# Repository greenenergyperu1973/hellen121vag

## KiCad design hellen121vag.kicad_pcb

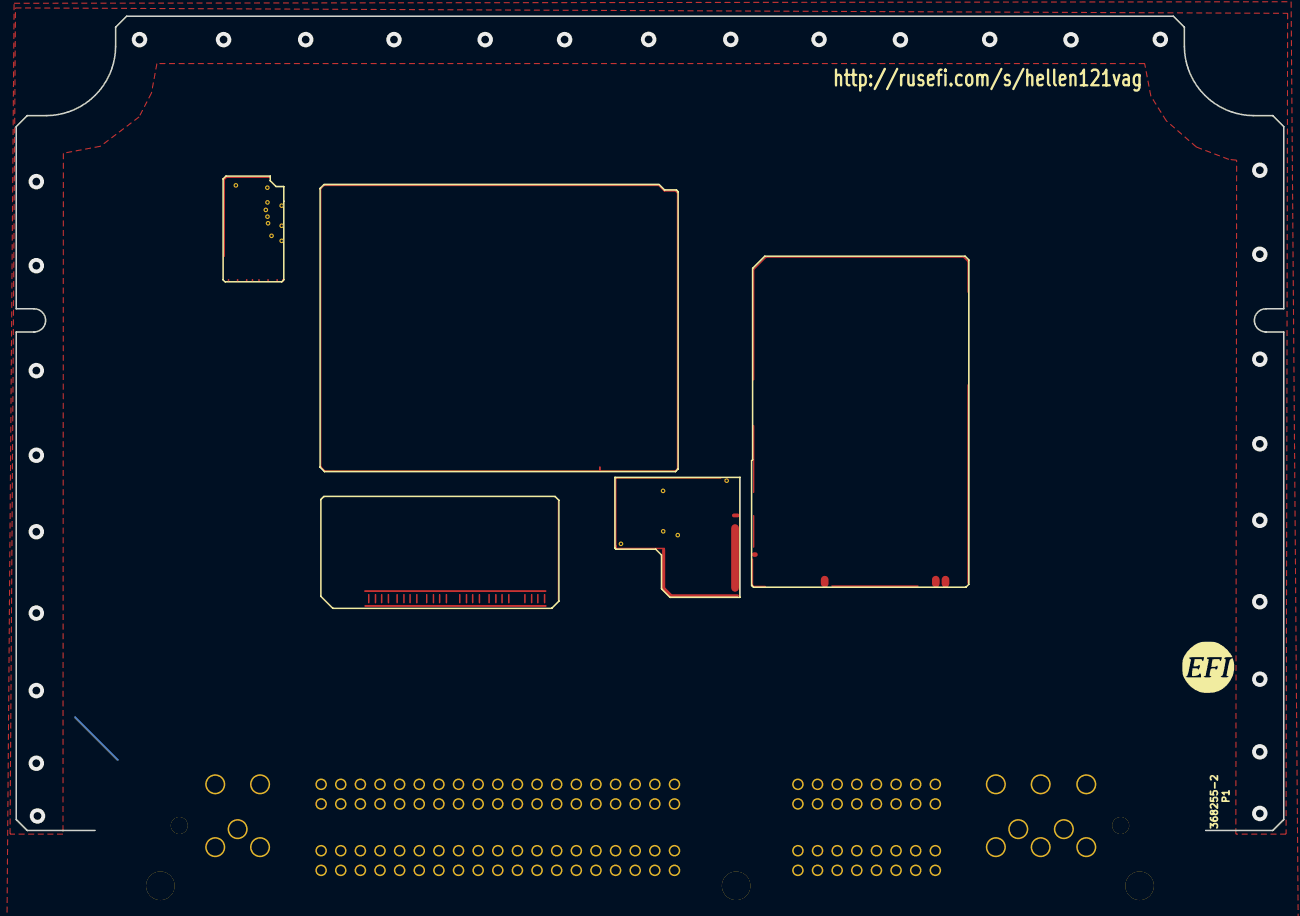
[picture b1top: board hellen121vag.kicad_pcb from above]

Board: 4 copper layers, 164.0 x 105.4 mm, 7 parts (0 on the bottom side), 108 nets.

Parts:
G7: LOGO
M3: Module-mcu-0.7; mcu
M4: Module-input-0.1; input
M6: Module-output-0.3; output
M7: Module-ign8-0.2; ign8
M8: Module-power12-0.2; power12
P1: 368255-2

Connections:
+5V: M3.S1 (V5), M4.E2 (V5), M6.W14 (V5), M8.E1 (V5)
+5VA: M3.S33 (V5A), M4.E5 (V5A), M4.J1 (PULL_V5A), M4.J5 (PULL_PPS), M4.J7 (PULL_AUX4), M4.J9 (PULL_AUX2), M4.J10 (PULL_AUX1), M4.J17 (PULL_CAM), M4.J18 (PULL_VSS), M4.J19 (PULL_TPS), M4.J20 (PULL_O2S), M4.J21 (PULL_CRANK), M4.N1 (V5A)
+5VP: P1.53, P1.72, P1.73, P1.83, P1.98
+12V_RAW: M6.S11 (V12_RAW), M8.E2 (V12_RAW)
/A1: M3.S30 (IN_O2S2), M4.N4 (O2S2)
/A2: M3.S22 (IN_MAP3), M4.N12 (MAP3)
/A3: M3.S26 (IN_AUX3), M4.N8 (AUX3)
/A4: M3.S23 (IN_DIG3), M4.N11 (RES3)
/AFR: M3.S16 (IN_O2S), M4.N18 (O2S)
/CAM1: M3.S15 (IN_AN_DIG2), M4.N19 (CAM)
/CAM2: M3.S27 (IN_AUX4), M4.N7 (AUX4)
/CHECK_ENGINE: M3.E22 (OUT_IO8), M6.W25 (LOW6_DIODE)
/CLT: M3.S18 (IN_CLT), M4.N16 (CLT)
/CRANK: M3.S13 (IN_AN_DIG1), M4.N21 (CRANK)
/D1: M3.S3 (IN_DIG8), M4.N26 (SENS1)
/D2: M3.S4 (IN_DIG9), M4.N25 (SENS2)
/D3: M3.S5 (IN_DIG10), M4.N24 (SENS3)
/D4: M3.S6 (IN_DIG11), M4.N23 (SENS4)
/FUEL_CONSUM: M3.E19 (OUT_PWM7), M6.W22 (PP2)
/FUEL_PUMP_RELAY: M3.E8 (OUT_IO1), M6.W35 (LOW11)
/IAT: M3.S19 (IN_IAT), M4.N15 (IAT)
/IDLE: M3.E23 (OUT_IO4), M6.W38 (LOW3_DUAL)
/IGN1: M3.W1 (OUT_IGN1), M7.V8 (IGN1)
/IGN2: M3.W2 (OUT_IGN2), M7.V7 (IGN2)
/IGN3: M3.W3 (OUT_IGN3), M7.V6 (IGN3)
/IGN4: M3.W4 (OUT_IGN4), M7.V5 (IGN4)
/IGN5: M3.W5 (OUT_IGN5), M7.V4 (IGN5)
/IGN6: M3.W6 (OUT_IGN6), M7.V3 (IGN6)
/IGN7: M3.W7 (OUT_IGN7), M7.V2 (IGN7)
/IGN8: M3.W8 (OUT_IGN8), M7.V1 (IGN8)
/IGN_V5: M3.W9 (IGN_V5), M7.V9 (VCC)
/IGN_V33: M3.W10 (IGN_V33), M7.V10 (V33)
/INJ1: M3.E25 (OUT_INJ1), M6.W24 (INJ1)
/INJ2: M3.E26 (OUT_INJ2), M6.W23 (INJ2)
/INJ3: M3.E29 (OUT_INJ3), M6.W20 (INJ3)
/INJ4: M3.E30 (OUT_INJ4), M6.W19 (INJ4)
/INJ5: M3.E31 (OUT_INJ5), M6.W18 (INJ5)
/INJ6: M3.E32 (OUT_INJ6), M6.W17 (INJ6)
/INJ7: M3.E33 (OUT_INJ7), M6.W16 (INJ7)
/INJ8: M3.E34 (OUT_INJ8), M6.W15 (INJ8)
/IN_AFR: M4.S9 (IN_O2S), P1.14
/IN_CAM1: M4.S5 (IN_CAM), P1.86
/IN_CAM2: M4.S21 (IN_AUX4), P1.87
/IN_CLT: M4.S15 (IN_CLT), P1.93
/IN_D1: M4.S1 (IN_SENS1), P1.55
/IN_D2: M4.S2 (IN_SENS2), P1.57
/IN_D3: M4.S3 (IN_SENS3), P1.75
/IN_D4: M4.S4 (IN_SENS4), P1.76
/IN_IAT: M4.S16 (IN_IAT), P1.26, P1.85
/IN_MAF: M4.S11 (IN_MAP1), P1.29
/IN_MAP2: M4.S12 (IN_MAP2), P1.101
/IN_PPS1: M4.S24 (IN_PPS), P1.34
/IN_PPS2: M4.S18 (IN_AUX2), P1.35
/IN_RES1: M4.S23 (IN_RES1), P1.38
/IN_RES2: M4.S26 (IN_RES2), P1.39
/IN_TPS1: M4.S10 (IN_TPS), P1.92
/IN_TPS2: M4.S17 (IN_AUX1), P1.84
/IN_VSS: M4.S6 (IN_VSS), P1.54
/KNOCK1: M3.S12 (IN_KNOCK), M4.N22 (KNOCK)
/MAF: M3.S20 (IN_MAP1), M4.N14 (MAP1)
/MAIN_RELAY: M3.E6 (OUT_IO3), M6.W40 (LOW5_MAIN)
/MAP2: M3.S21 (IN_MAP2), M4.N13 (MAP2)
/OUT1: M3.E7 (OUT_IO5), M6.W39 (LOW7_HIGH1)
/OUT2: M3.E9 (OUT_IO6), M6.W37 (LOW8_HIGH2)
/OUT3: M3.E28 (OUT_PWM8), M6.W21 (LOW1)
/OUT_CHECK_ENGINE: M6.W3 (OUT_LOW6_DIODE), P1.47
/OUT_FUEL_CONSUM: M6.S6 (OUT_PP2), P1.81
/OUT_FUEL_PUMP_RELAY: M6.S10 (OUT_LOW11), P1.65
/OUT_IDLE: M6.S7 (OUT_LOW3_DUAL), P1.105
/OUT_IGN1: M7.S8 (OUT_IGN1), P1.102
/OUT_IGN2: M7.S7 (OUT_IGN2), P1.7
/OUT_IGN3: M7.S6 (OUT_IGN3), P1.111
/OUT_IGN4: M7.S5 (OUT_IGN4), P1.94
/OUT_IGN5: M7.S4 (OUT_IGN5), P1.103
/OUT_IGN6: M7.S3 (OUT_IGN6), P1.110
/OUT_IGN7: M7.S2 (OUT_IGN7), P1.8
/OUT_IGN8: M7.S1 (OUT_IGN8), P1.95
/OUT_INJ1: M6.S18 (OUT_INJ1), P1.96
/OUT_INJ2: M6.S16 (OUT_INJ2), P1.89
/OUT_INJ3: M6.S17 (OUT_INJ3), P1.97
/OUT_INJ4: M6.W7 (OUT_INJ4), P1.88
/OUT_INJ5: M6.W10 (OUT_INJ5), P1.113
/OUT_INJ6: M6.S15 (OUT_INJ6), P1.112
/OUT_INJ7: M6.W12 (OUT_INJ7), P1.19
/OUT_INJ8: M6.W11 (OUT_INJ8), P1.24
/OUT_VVT1_1: M6.S13 (OUT_LOW12), M6.S14 (OUT_LOW9), P1.22
/OUT_VVT1_2: M6.W1 (OUT_LOW2), M6.W2 (OUT_LOW10), P1.115
/OUT_VVT2_B1: M6.S5 (OUT_SOLENOID_B2), P1.18
/OUT_VVT2_B2: M6.S4 (OUT_SOLENOID_B1), P1.120
/OUT_WASTEGATE: M6.W4 (OUT_LOW4_DUAL), P1.104
/PPS1: M3.S29 (IN_PPS), M4.N5 (PPS)
/PPS2: M3.S25 (IN_AUX2), M4.N9 (AUX2)
/RES1: M3.S28 (IN_DIG1), M4.N6 (RES1)
/RES2: M3.S31 (IN_DIG2), M4.N3 (RES2)
/TACH: M3.E27 (OUT_PWM1), M6.W28 (PP1)
/TPS1: M3.S17 (IN_TPS), M4.N17 (TPS)
/TPS2: M3.S24 (IN_AUX1), M4.N10 (AUX1)
/V12_PERM: M8.V4 (V12_PERM), P1.62
/VBAT: M3.N17 (VBAT), M8.V2 (VBAT)
/VIGN: M3.S7 (VIGN), M8.V5 (VIGN)
/VSS: M3.S14 (IN_AN_DIG3), M4.N20 (VSS)
/VVT1_1: M3.E10 (OUT_IO10), M6.W27 (LOW9), M6.W36 (LOW12)
/VVT1_2: M3.E21 (OUT_IO7), M6.W26 (LOW10), M6.W29 (LOW2)
/VVT2_B1: M3.E17 (OUT_PWM5), M6.W30 (SOLENOID_B2)
/VVT2_B2: M3.E16 (OUT_PWM4), M6.W31 (SOLENOID_B1)
/WASTEGATE: M3.E12 (OUT_IO2), M6.W34 (LOW4_DUAL)
GND: M3.S2 (GND), M4.E1 (GND), M6.G (GND), M6.S3 (GND), M7.G (GND), M8.S1 (GND), P1.1, P1.2, P1.32, P1.59
GNDA: M3.S32 (GNDA), M4.J2 (PULL_GNDA), M4.J3 (PULL_RES2), M4.J4 (PULL_O2S2), M4.J6 (PULL_RES1), M4.J8 (PULL_AUX3), M4.J11 (PULL_RES3), M4.J12 (PULL_MAP3), M4.J13 (PULL_MAP2), M4.J14 (PULL_MAP1), M4.J22 (PULL_KNOCK), M4.J23 (PULL_SENS4), M4.J24 (PULL_SENS3), M4.J25 (PULL_SENS2), M4.J26 (PULL_SENS1), M4.N2 (GNDA), P1.27, P1.33, P1.36, P1.50, P1.91, P1.99, P1.108

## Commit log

2025-11-14 Primer commit: subiendo proyecto hellen121vag completo
2025-11-14 modifique la pcb
2025-11-14 el archivo revision agregue laversion d
2025-11-14 [skip actions] Auto-generated board
